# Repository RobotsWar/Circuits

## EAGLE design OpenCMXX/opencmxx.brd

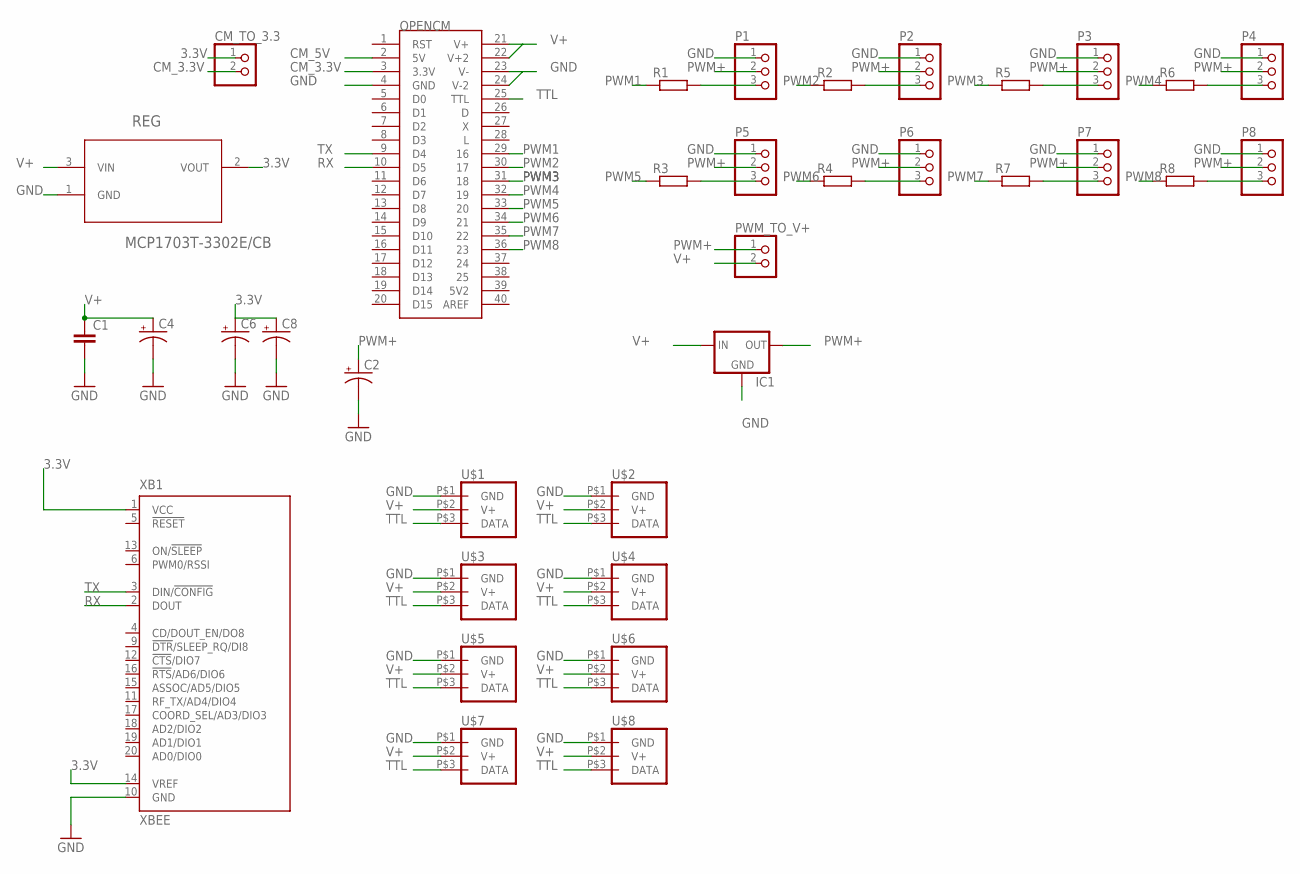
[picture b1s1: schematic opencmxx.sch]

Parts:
C1: C-EU075-032X103; C075-032X103
C2, C4, C6, C8: CAP_POLPTH2; CPOL-RADIAL-10UF-25V
CM_TO_3.3: CONNEC_1X02
IC1: V_REG_78XXSIDE; 78XXL
OPENCM: OPENCM
P1, P2, P3, P4, P5, P6, P7, P8: CONNEC_1X03
PWM_TO_V+: CONNEC_1X02
R1, R2, R3, R4, R5, R6, R7, R8: RESISTANCE-R0805; R0805
REG: MCP1703T-3302E/CB; SOT95P300X145-3N
U$1, U$2, U$3, U$4, U$5, U$6, U$7, U$8: XL_320_CONNEC; DXL_320_CONNEC
XB1: XBEE

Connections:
3.3V: C6.1 (+), C8.1 (+), CM_TO_3.3.1, REG.2 (VOUT), XB1.1 (VCC), XB1.14 (VREF)
CM_3.3V: CM_TO_3.3.2, OPENCM.3 (3.3V)
CM_5V: OPENCM.2 (5V)
GND: C1.2, C2.2 (-), C4.2 (-), C6.2 (-), C8.2 (-), IC1.GND, OPENCM.4 (GND), OPENCM.23 (V-), OPENCM.24 (V-2), P1.1, P2.1, P3.1, P4.1, P5.1, P6.1, P7.1, P8.1, REG.1 (GND), U$1.P$1 (GND), U$2.P$1 (GND), U$3.P$1 (GND), U$4.P$1 (GND), U$5.P$1 (GND), U$6.P$1 (GND), U$7.P$1 (GND), U$8.P$1 (GND), XB1.10 (GND)
unnamed: P2.3, R2.2
unnamed: P1.3, R1.2
unnamed: P5.3, R3.2
unnamed: P6.3, R4.2
unnamed: P3.3, R5.2
unnamed: P4.3, R6.2
unnamed: P7.3, R7.2
unnamed: P8.3, R8.2
PWM1: OPENCM.29 (16), R1.1
PWM2: OPENCM.30 (17), R2.1
PWM3: OPENCM.31 (18), R5.1
PWM4: OPENCM.32 (19), R6.1
PWM5: OPENCM.33 (20), R3.1
PWM6: OPENCM.34 (21), R4.1
PWM7: OPENCM.35 (22), R7.1
PWM8: OPENCM.36 (23), R8.1
PWM+: C2.1 (+), IC1.OUT, P1.2, P2.2, P3.2, P4.2, P5.2, P6.2, P7.2, P8.2, PWM_TO_V+.1
RX: OPENCM.10 (D5), XB1.2 (DOUT)
TTL: OPENCM.25 (TTL), U$1.P$3 (DATA), U$2.P$3 (DATA), U$3.P$3 (DATA), U$4.P$3 (DATA), U$5.P$3 (DATA), U$6.P$3 (DATA), U$7.P$3 (DATA), U$8.P$3 (DATA)
TX: OPENCM.9 (D4), XB1.3 (DIN/!CONFIG)
V+: C1.1, C4.1 (+), IC1.IN, OPENCM.21 (V+), OPENCM.22 (V+2), PWM_TO_V+.2, REG.3 (VIN), U$1.P$2 (V+), U$2.P$2 (V+), U$3.P$2 (V+), U$4.P$2 (V+), U$5.P$2 (V+), U$6.P$2 (V+), U$7.P$2 (V+), U$8.P$2 (V+)

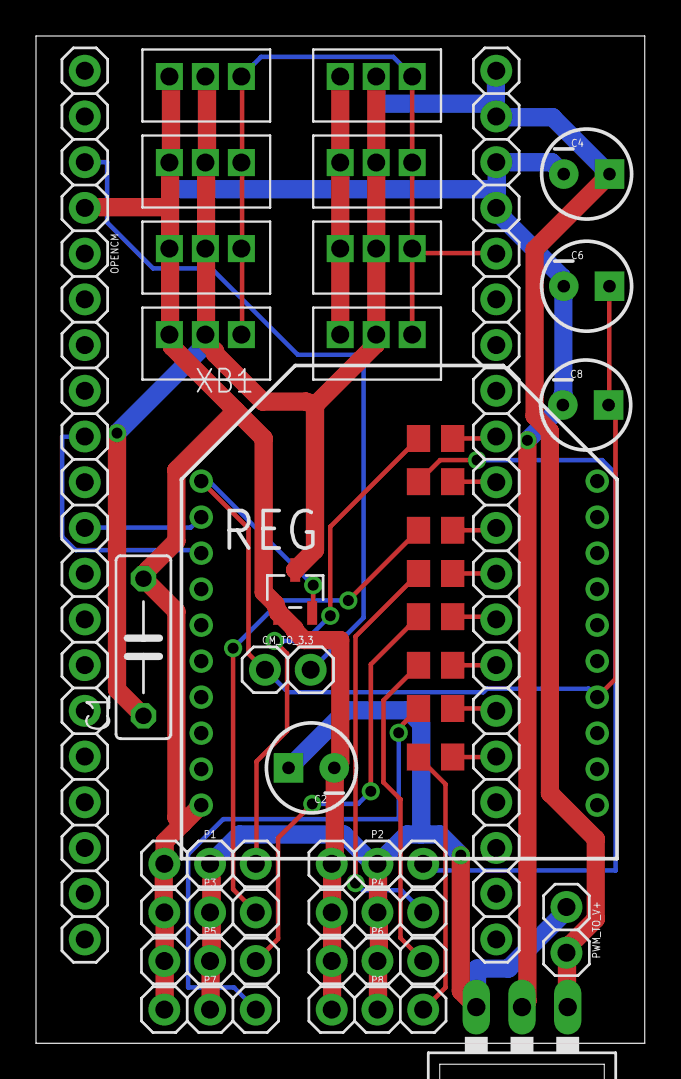
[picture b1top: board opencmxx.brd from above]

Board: 2 copper layers, 33.8 x 56.0 mm, 35 parts (0 on the bottom side), 24 nets.

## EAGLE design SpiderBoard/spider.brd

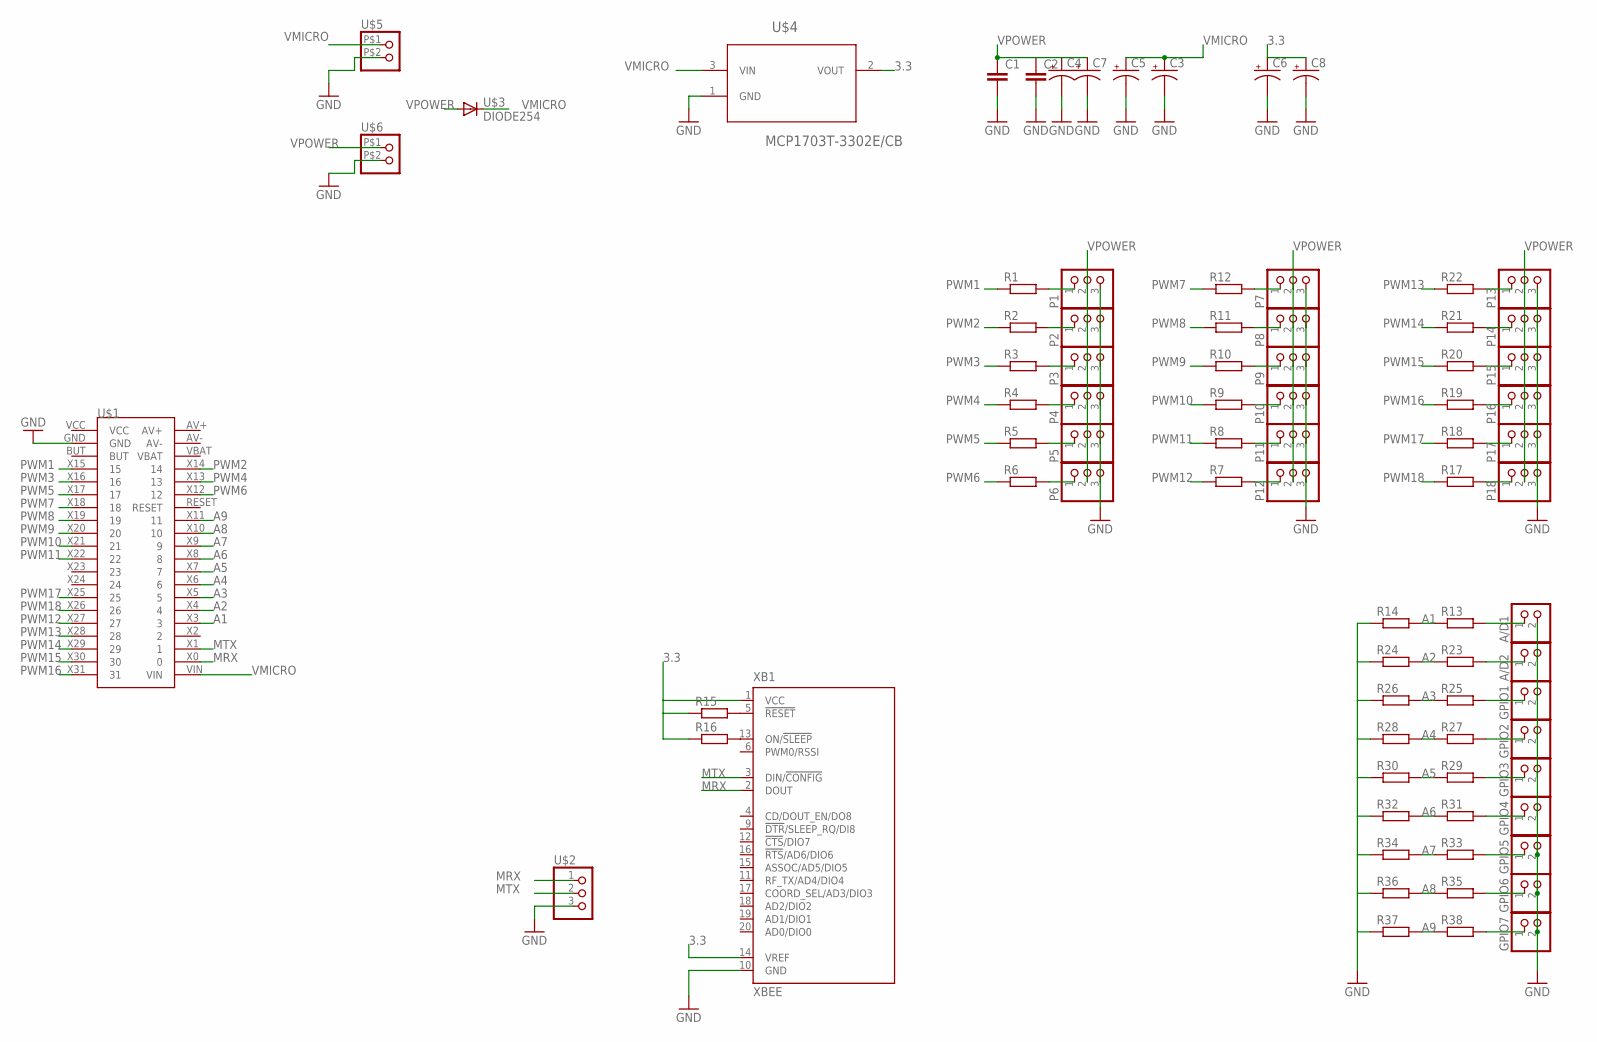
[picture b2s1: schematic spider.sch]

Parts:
A/D1, A/D2: CONNEC_1X02
C1, C2: C-EU075-032X103; C075-032X103
C3, C4, C5, C6, C7, C8: CAP_POLPTH2; CPOL-RADIAL-10UF-25V
GPIO1, GPIO2, GPIO3, GPIO4, GPIO5, GPIO6, GPIO7: CONNEC_1X02
P1, P2, P3, P4, P5, P6, P7, P8, P9, P10, P11, P12, P13, P14, P15, P16, P17, P18: CONNEC_1X03
R1, R2, R3, R4, R5, R6, R7, R8, R9, R10, R11, R12, R13, R14, R17, R18, R19, R20, R21, R22, R23, R24, R25, R26, R27, R28, R29, R30, R31, R32, R33, R34, R35, R36, R37, R38: RESISTANCE-R0805; R0805
R15, R16: R-EU_R0805; R0805
U$1: MAPLE_MINI; CONNEC_2X20
U$2: CONNEC_1X03
U$3: DIODE254; DIODE_254
U$4: MCP1703T-3302E/CB; SOT95P300X145-3N
U$5, U$6: CONNEC_1X02BIG; CONNEC_1X02_BIG
XB1: XBEE

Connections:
3.3: C6.1 (+), C8.1 (+), R15.1, R16.1, U$4.2 (VOUT), XB1.1 (VCC), XB1.14 (VREF)
A1: R13.1, R14.2, U$1.X3 (3)
A1P: A/D1.1, R13.2
A2: R23.1, R24.2, U$1.X4 (4)
A2P: A/D2.1, R23.2
A3: R25.1, R26.2, U$1.X5 (5)
A3P: GPIO1.1, R25.2
A4: R27.1, R28.2, U$1.X6 (6)
A4P: GPIO2.1, R27.2
A5: R29.1, R30.2, U$1.X7 (7)
A5P: GPIO3.1, R29.2
A6: R31.1, R32.2, U$1.X8 (8)
A6P: GPIO4.1, R31.2
A7: R33.1, R34.2, U$1.X9 (9)
A7P: GPIO5.1, R33.2
A8: R35.1, R36.2, U$1.X10 (10)
A8P: GPIO6.1, R35.2
A9: R37.2, R38.1, U$1.X11 (11)
GND: A/D1.2, A/D2.2, C1.2, C2.2, C3.2 (-), C4.2 (-), C5.2 (-), C6.2 (-), C7.2 (-), C8.2 (-), GPIO1.2, GPIO2.2, GPIO3.2, GPIO4.2, GPIO5.2, GPIO6.2, GPIO7.2, P1.3, P2.3, P3.3, P4.3, P5.3, P6.3, P7.3, P8.3, P9.3, P10.3, P11.3, P12.3, P13.3, P14.3, P15.3, P16.3, P17.3, P18.3, R14.1, R24.1, R26.1, R28.1, R30.1, R32.1, R34.1, R36.1, R37.1, U$1.GND, U$2.3, U$4.1 (GND), U$5.P$2 (2), U$6.P$2 (2), XB1.10 (GND)
MRX: U$1.X0 (0), U$2.1, XB1.2 (DOUT)
MTX: U$1.X1 (1), U$2.2, XB1.3 (DIN/!CONFIG)
unnamed: P1.1, R1.2
unnamed: P2.1, R2.2
unnamed: P3.1, R3.2
unnamed: P4.1, R4.2
unnamed: P5.1, R5.2
unnamed: P6.1, R6.2
unnamed: P12.1, R7.2
unnamed: P11.1, R8.2
unnamed: P10.1, R9.2
unnamed: P9.1, R10.2
unnamed: P8.1, R11.2
unnamed: P7.1, R12.2
unnamed: R15.2, XB1.5 (!RESET)
unnamed: P18.1, R17.2
unnamed: R16.2, XB1.13 (ON/!SLEEP)
unnamed: P17.1, R18.2
unnamed: P16.1, R19.2
unnamed: P15.1, R20.2
unnamed: P14.1, R21.2
unnamed: P13.1, R22.2
unnamed: GPIO7.1, R38.2
PWM1: R1.1, U$1.X15 (15)
PWM2: R2.1, U$1.X14 (14)
PWM3: R3.1, U$1.X16 (16)
PWM4: R4.1, U$1.X13 (13)
PWM5: R5.1, U$1.X17 (17)
PWM6: R6.1, U$1.X12 (12)
PWM7: R12.1, U$1.X18 (18)
PWM8: R11.1, U$1.X19 (19)
PWM9: R10.1, U$1.X20 (20)
PWM10: R9.1, U$1.X21 (21)
PWM11: R8.1, U$1.X22 (22)
PWM12: R7.1, U$1.X27 (27)
PWM13: R22.1, U$1.X28 (28)
PWM14: R21.1, U$1.X29 (29)
PWM15: R20.1, U$1.X30 (30)
PWM16: R19.1, U$1.X31 (31)
PWM17: R18.1, U$1.X25 (25)
PWM18: R17.1, U$1.X26 (26)
VMICRO: C3.1 (+), C5.1 (+), U$1.VIN, U$3.B (C), U$4.3 (VIN), U$5.P$1 (1)
VPOWER: C1.1, C2.1, C4.1 (+), C7.1 (+), P1.2, P2.2, P3.2, P4.2, P5.2, P6.2, P7.2, P8.2, P9.2, P10.2, P11.2, P12.2, P13.2, P14.2, P15.2, P16.2, P17.2, P18.2, U$3.A, U$6.P$1 (1)

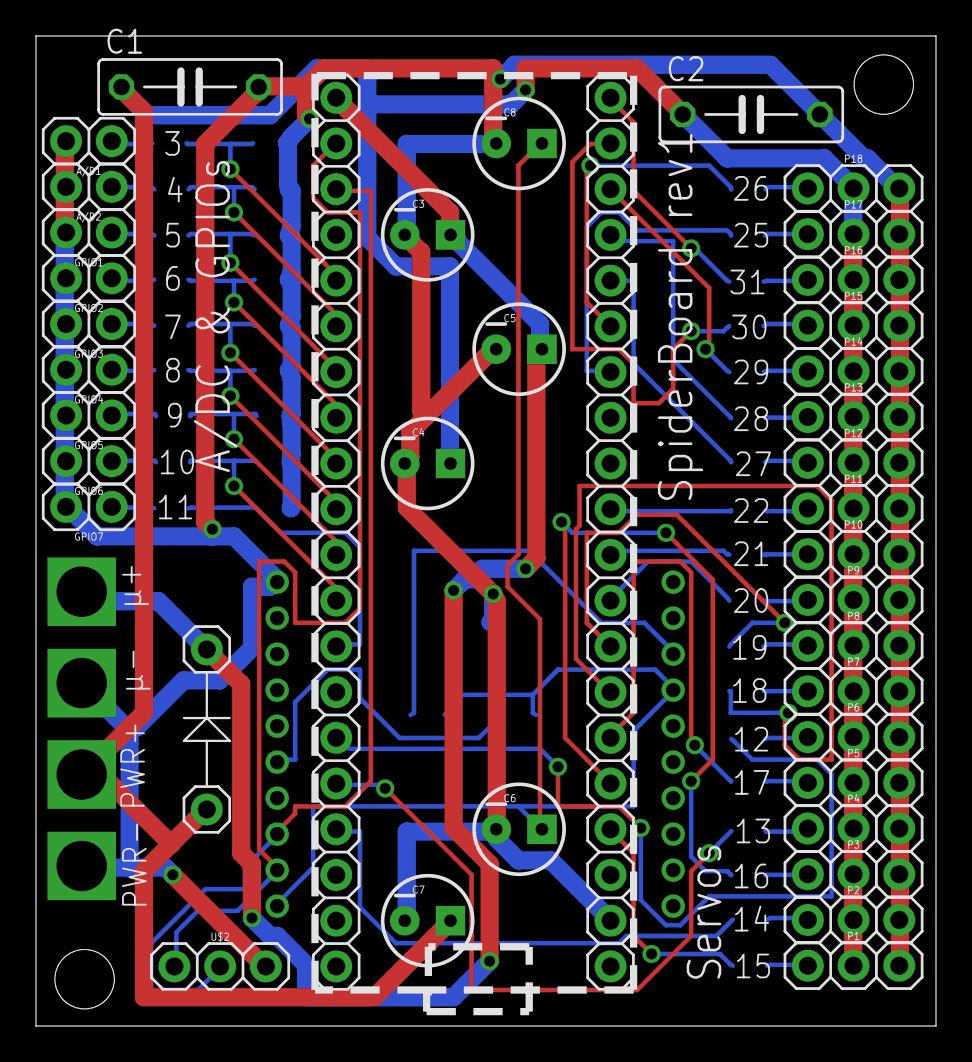
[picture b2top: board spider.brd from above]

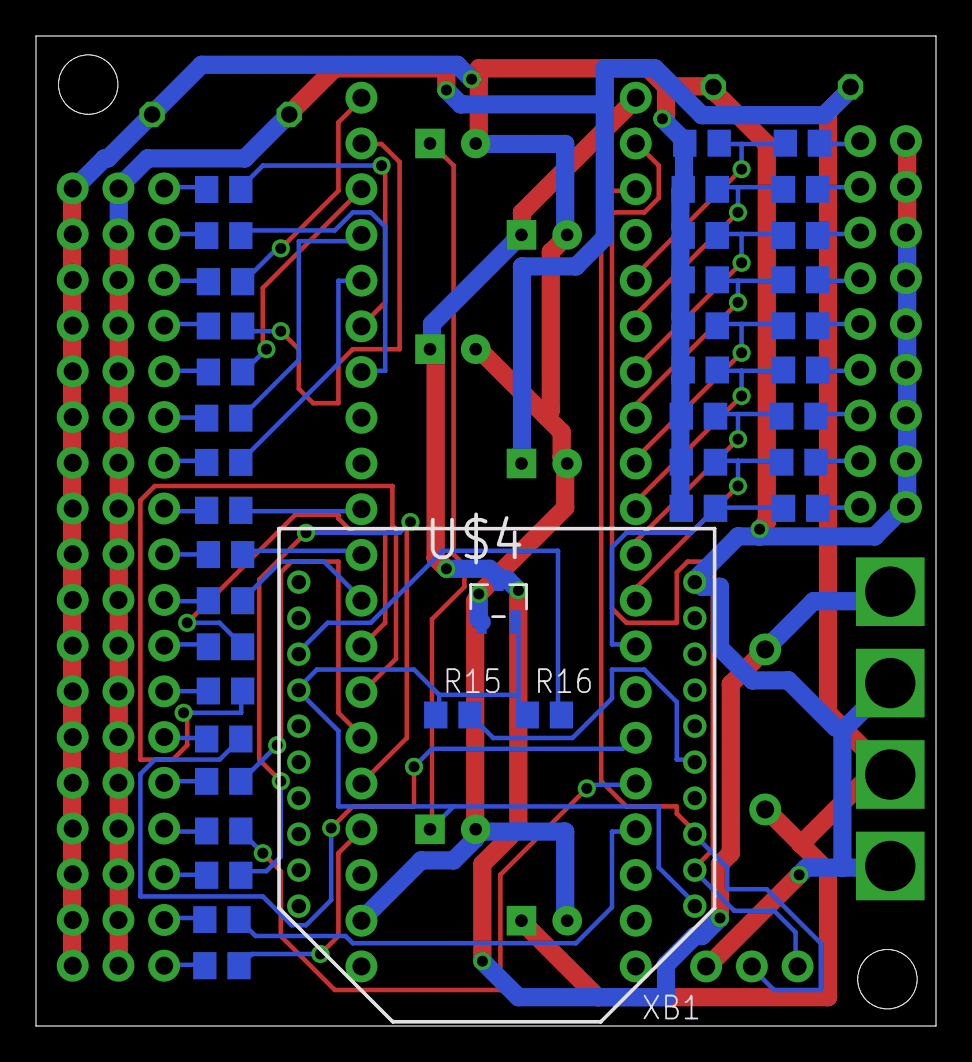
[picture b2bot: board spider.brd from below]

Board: 2 copper layers, 50.0 x 55.0 mm, 82 parts (40 on the bottom side), 62 nets.

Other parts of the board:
U$7, U$9: STAND-OFF

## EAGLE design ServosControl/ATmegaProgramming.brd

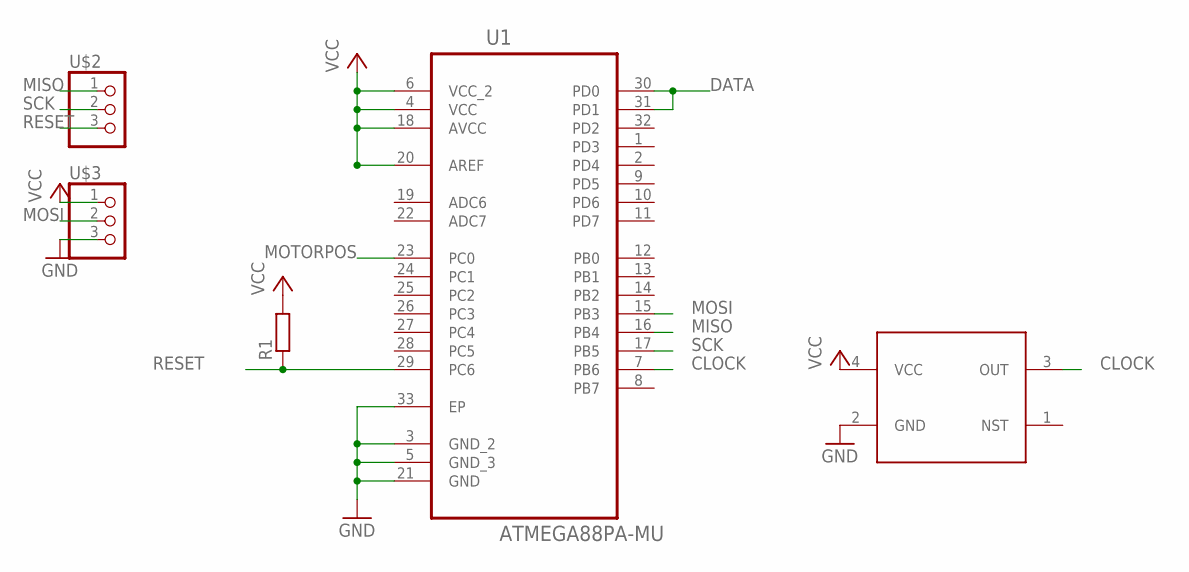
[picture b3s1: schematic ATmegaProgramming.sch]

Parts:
R1: R-EU_0414/15; 0414/15
U1: ATMEGA88PA-MU; QFN50P500X500X100-33N
U$1: SG-310
U$2, U$3: CONNEC_1X03

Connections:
CLOCK: U1.7 (PB6), U$1.3 (OUT)
DATA: U1.30 (PD0), U1.31 (PD1)
GND: U1.3 (GND_2), U1.5 (GND_3), U1.21 (GND), U1.33 (EP), U$1.2 (GND), U$3.3
MISO: U1.16 (PB4), U$2.1
MOSI: U1.15 (PB3), U$3.2
MOTORPOS: U1.23 (PC0)
RESET: R1.1, U1.29 (PC6), U$2.3
SCK: U1.17 (PB5), U$2.2
VCC: R1.2, U1.4 (VCC), U1.6 (VCC_2), U1.18 (AVCC), U1.20 (AREF), U$1.4 (VCC), U$3.1

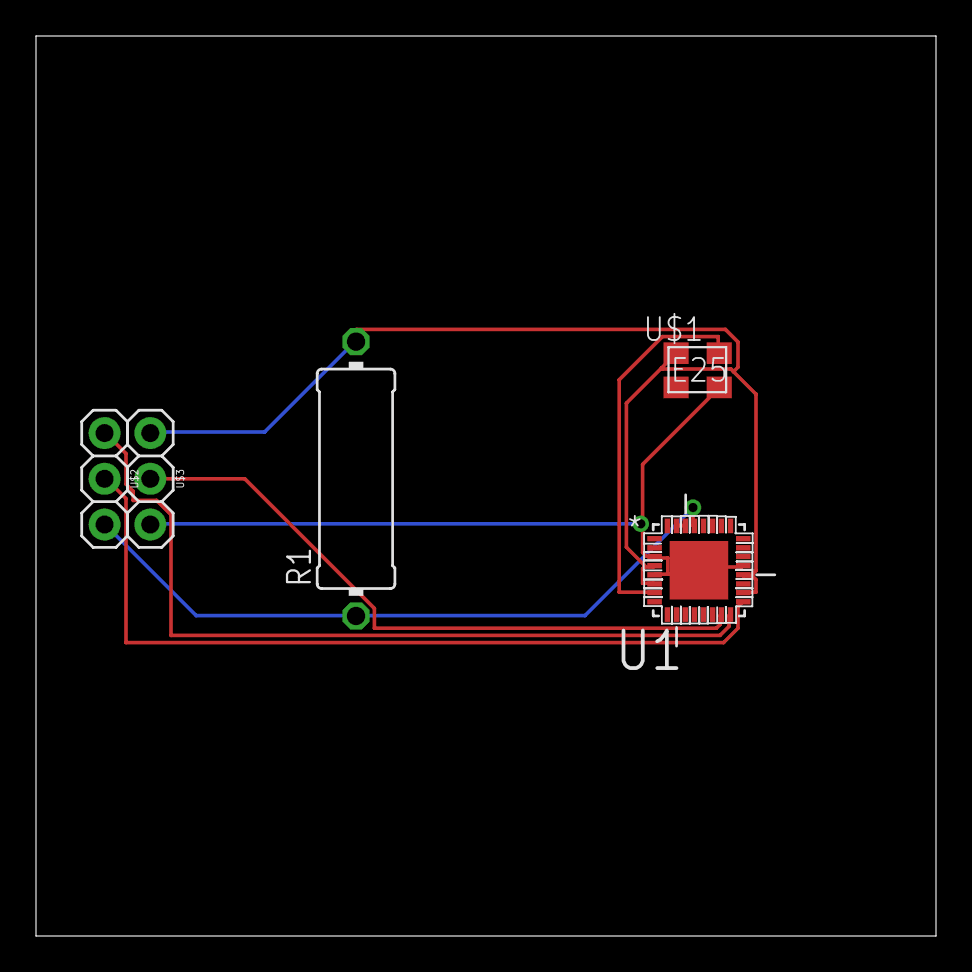
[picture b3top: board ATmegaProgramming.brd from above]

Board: 2 copper layers, 50.0 x 50.0 mm, 5 parts (0 on the bottom side), 8 nets.

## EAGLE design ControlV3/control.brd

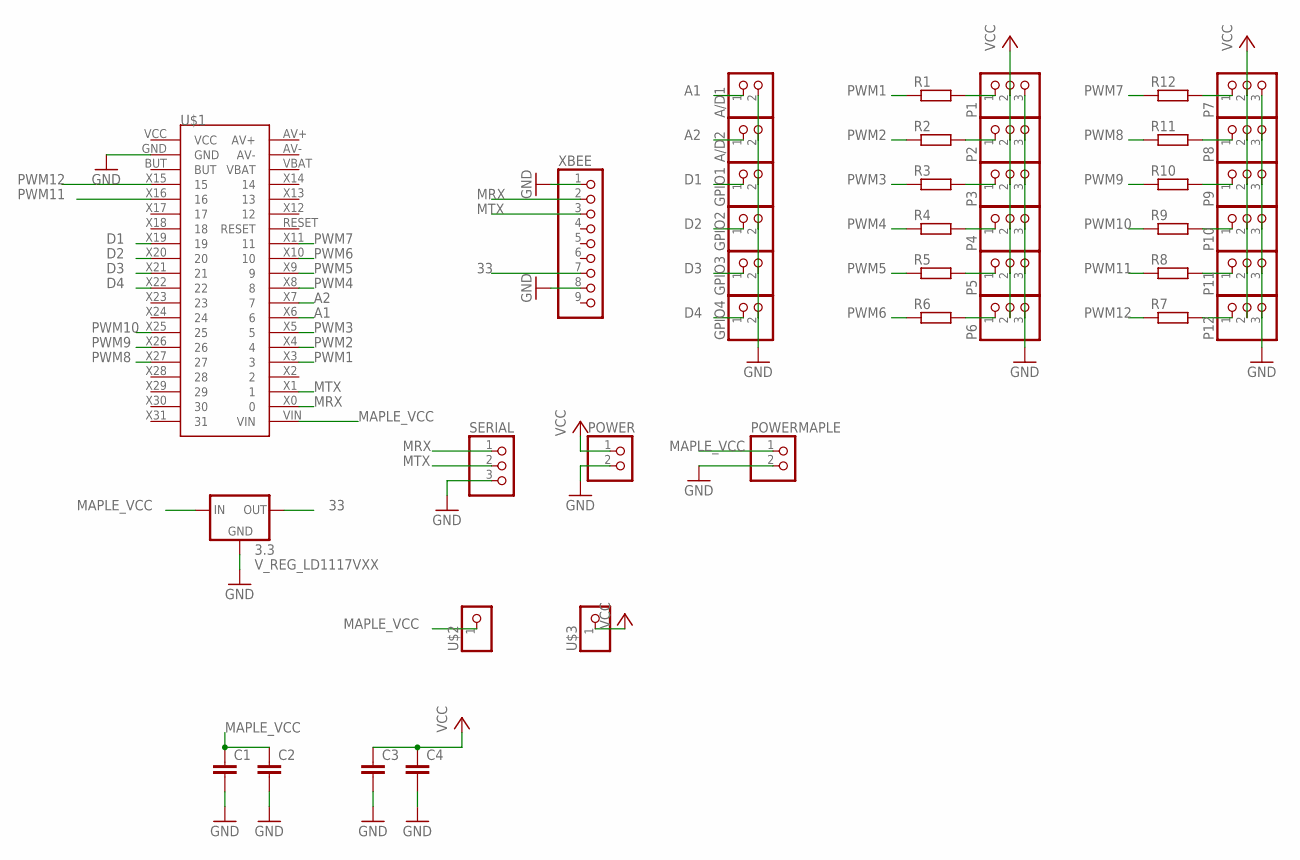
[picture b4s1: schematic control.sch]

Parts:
3.3: V_REG_LD1117VXX; 78XXL
A/D1, A/D2: CONNEC_1X02
C1, C2, C3, C4: C-EU075-032X103; C075-032X103
GPIO1, GPIO2, GPIO3, GPIO4: CONNEC_1X02
P1, P2, P3, P4, P5, P6, P7, P8, P9, P10, P11, P12: CONNEC_1X03
POWER: CONNEC_1X02
POWERMAPLE: CONNEC_1X02
R1, R2, R3, R4, R5, R6, R7, R8, R9, R10, R11, R12: RESISTANCE-R0805; R0805
SERIAL: CONNEC_1X03
U$1: MAPLE_MINI; CONNEC_2X20
U$2, U$3: CONNEC_1X01
XBEE: CONNEC_1X09

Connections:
33: 3.3.GND (OUT), XBEE.7
A1: A/D1.1, U$1.X6 (6)
A2: A/D2.1, U$1.X7 (7)
D1: GPIO1.1, U$1.X19 (19)
D2: GPIO2.1, U$1.X20 (20)
D3: GPIO3.1, U$1.X21 (21)
D4: GPIO4.1, U$1.X22 (22)
GND: 3.3.IN (GND), A/D1.2, A/D2.2, C1.2, C2.2, C3.2, C4.2, GPIO1.2, GPIO2.2, GPIO3.2, GPIO4.2, P1.3, P2.3, P3.3, P4.3, P5.3, P6.3, P7.3, P8.3, P9.3, P10.3, P11.3, P12.3, POWER.2, POWERMAPLE.2, SERIAL.3, U$1.GND, XBEE.1, XBEE.8
MAPLE_VCC: 3.3.OUT (IN), C1.1, C2.1, POWERMAPLE.1, U$1.VIN, U$2.1
MRX: SERIAL.1, U$1.X0 (0), XBEE.2
MTX: SERIAL.2, U$1.X1 (1), XBEE.3
unnamed: P1.1, R1.2
unnamed: P2.1, R2.2
unnamed: P3.1, R3.2
unnamed: P4.1, R4.2
unnamed: P5.1, R5.2
unnamed: P6.1, R6.2
unnamed: P12.1, R7.2
unnamed: P11.1, R8.2
unnamed: P10.1, R9.2
unnamed: P9.1, R10.2
unnamed: P8.1, R11.2
unnamed: P7.1, R12.2
PWM1: R1.1, U$1.X3 (3)
PWM2: R2.1, U$1.X4 (4)
PWM3: R3.1, U$1.X5 (5)
PWM4: R4.1, U$1.X8 (8)
PWM5: R5.1, U$1.X9 (9)
PWM6: R6.1, U$1.X10 (10)
PWM7: R12.1, U$1.X11 (11)
PWM8: R11.1, U$1.X27 (27)
PWM9: R10.1, U$1.X26 (26)
PWM10: R9.1, U$1.X25 (25)
PWM11: R8.1, U$1.X16 (16)
PWM12: R7.1, U$1.X15 (15)
VCC: C3.1, C4.1, P1.2, P2.2, P3.2, P4.2, P5.2, P6.2, P7.2, P8.2, P9.2, P10.2, P11.2, P12.2, POWER.1, U$3.1

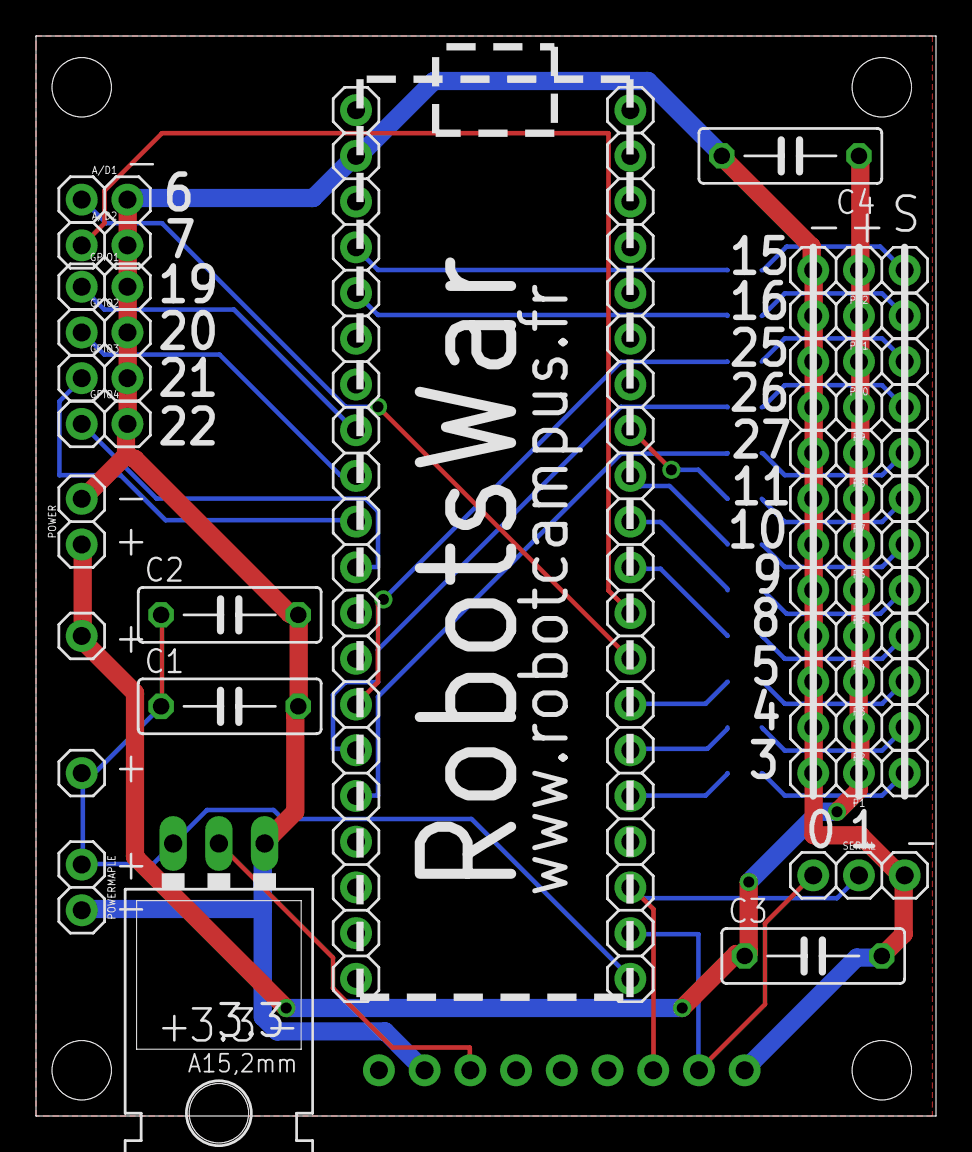
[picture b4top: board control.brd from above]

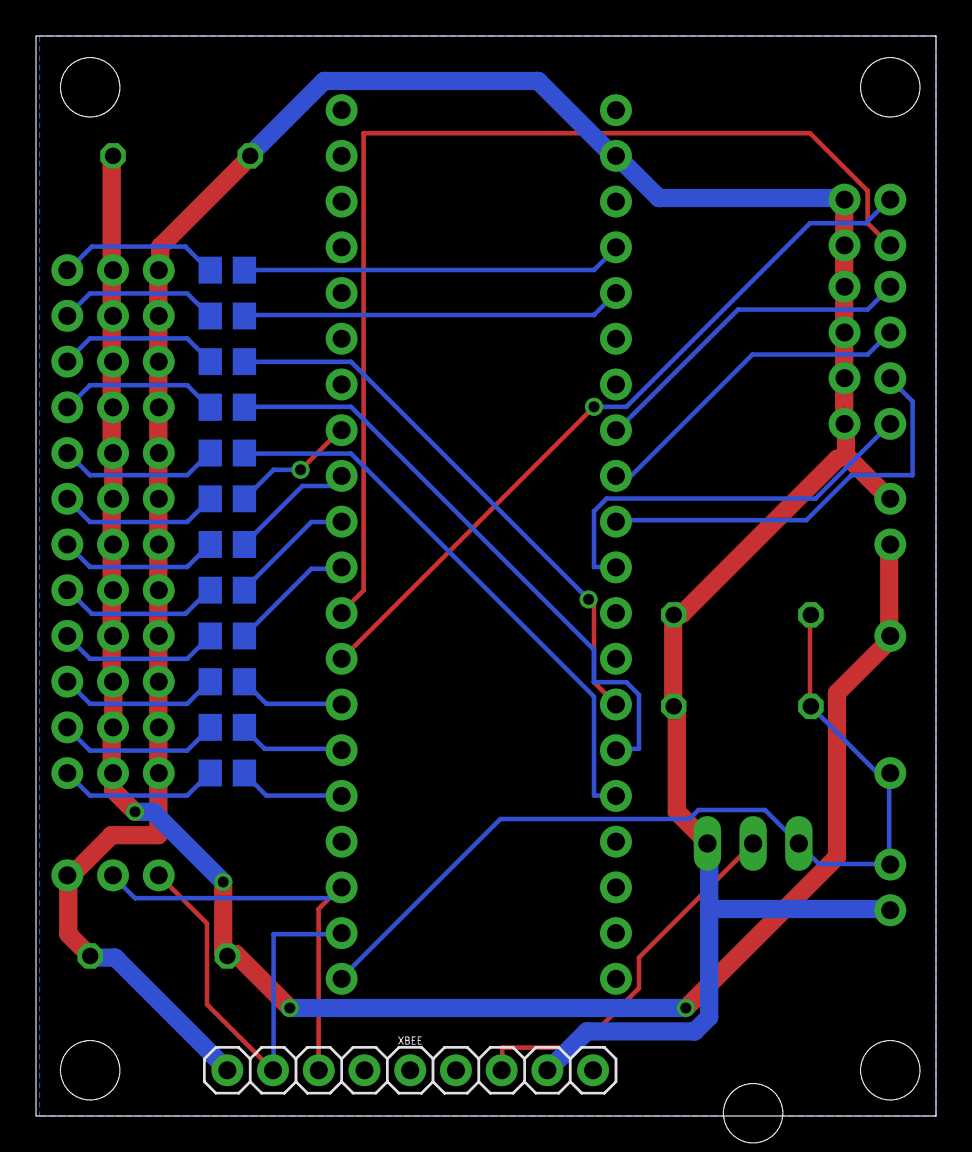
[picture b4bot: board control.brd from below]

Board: 2 copper layers, 50.0 x 60.0 mm, 46 parts (13 on the bottom side), 36 nets.

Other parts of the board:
U$4, U$5, U$6, U$7: STAND-OFF

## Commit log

2013-01-31 Adding ControlV3 and Library
2013-01-31 Removing EPFs
2013-01-31 Removing PRO
2013-02-04 Adding ATMega8 MLF programming
2013-02-04 Adding cam
2013-02-04 Updating board
2013-02-12 Adding PDF
2013-08-26 ControlV4: composants
2013-09-03 Fabien V4
2013-09-03 Ajout du MCP à la lib
2013-09-03 Removing unused XBee port, changing extra serial port to 2.54
2013-09-03 Ajout diode 2.54
2013-09-03 Fixs
2013-09-03 Boarding
2013-09-03 Adding DIODE254 to lib
2013-09-03 Adding diode TO252AA
2013-09-03 Moving to official package for diode
2013-09-03 First version full autorouted
2013-09-04 Ajout du logo sérigraphié
2013-09-04 Ajout du cam
2013-09-05 Fixing the 33/3.3 problem
2013-11-26 SpiderBoard
2014-03-20 Adding OpenCM footprint
2014-03-20 OpenCM++
2014-04-07 OpenCMXX

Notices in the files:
parts and their libraries:
SparkFun-PowerIC: Licensing: CC v3.0 Share-Alike You are welcome to use this library for commercial purposes.
